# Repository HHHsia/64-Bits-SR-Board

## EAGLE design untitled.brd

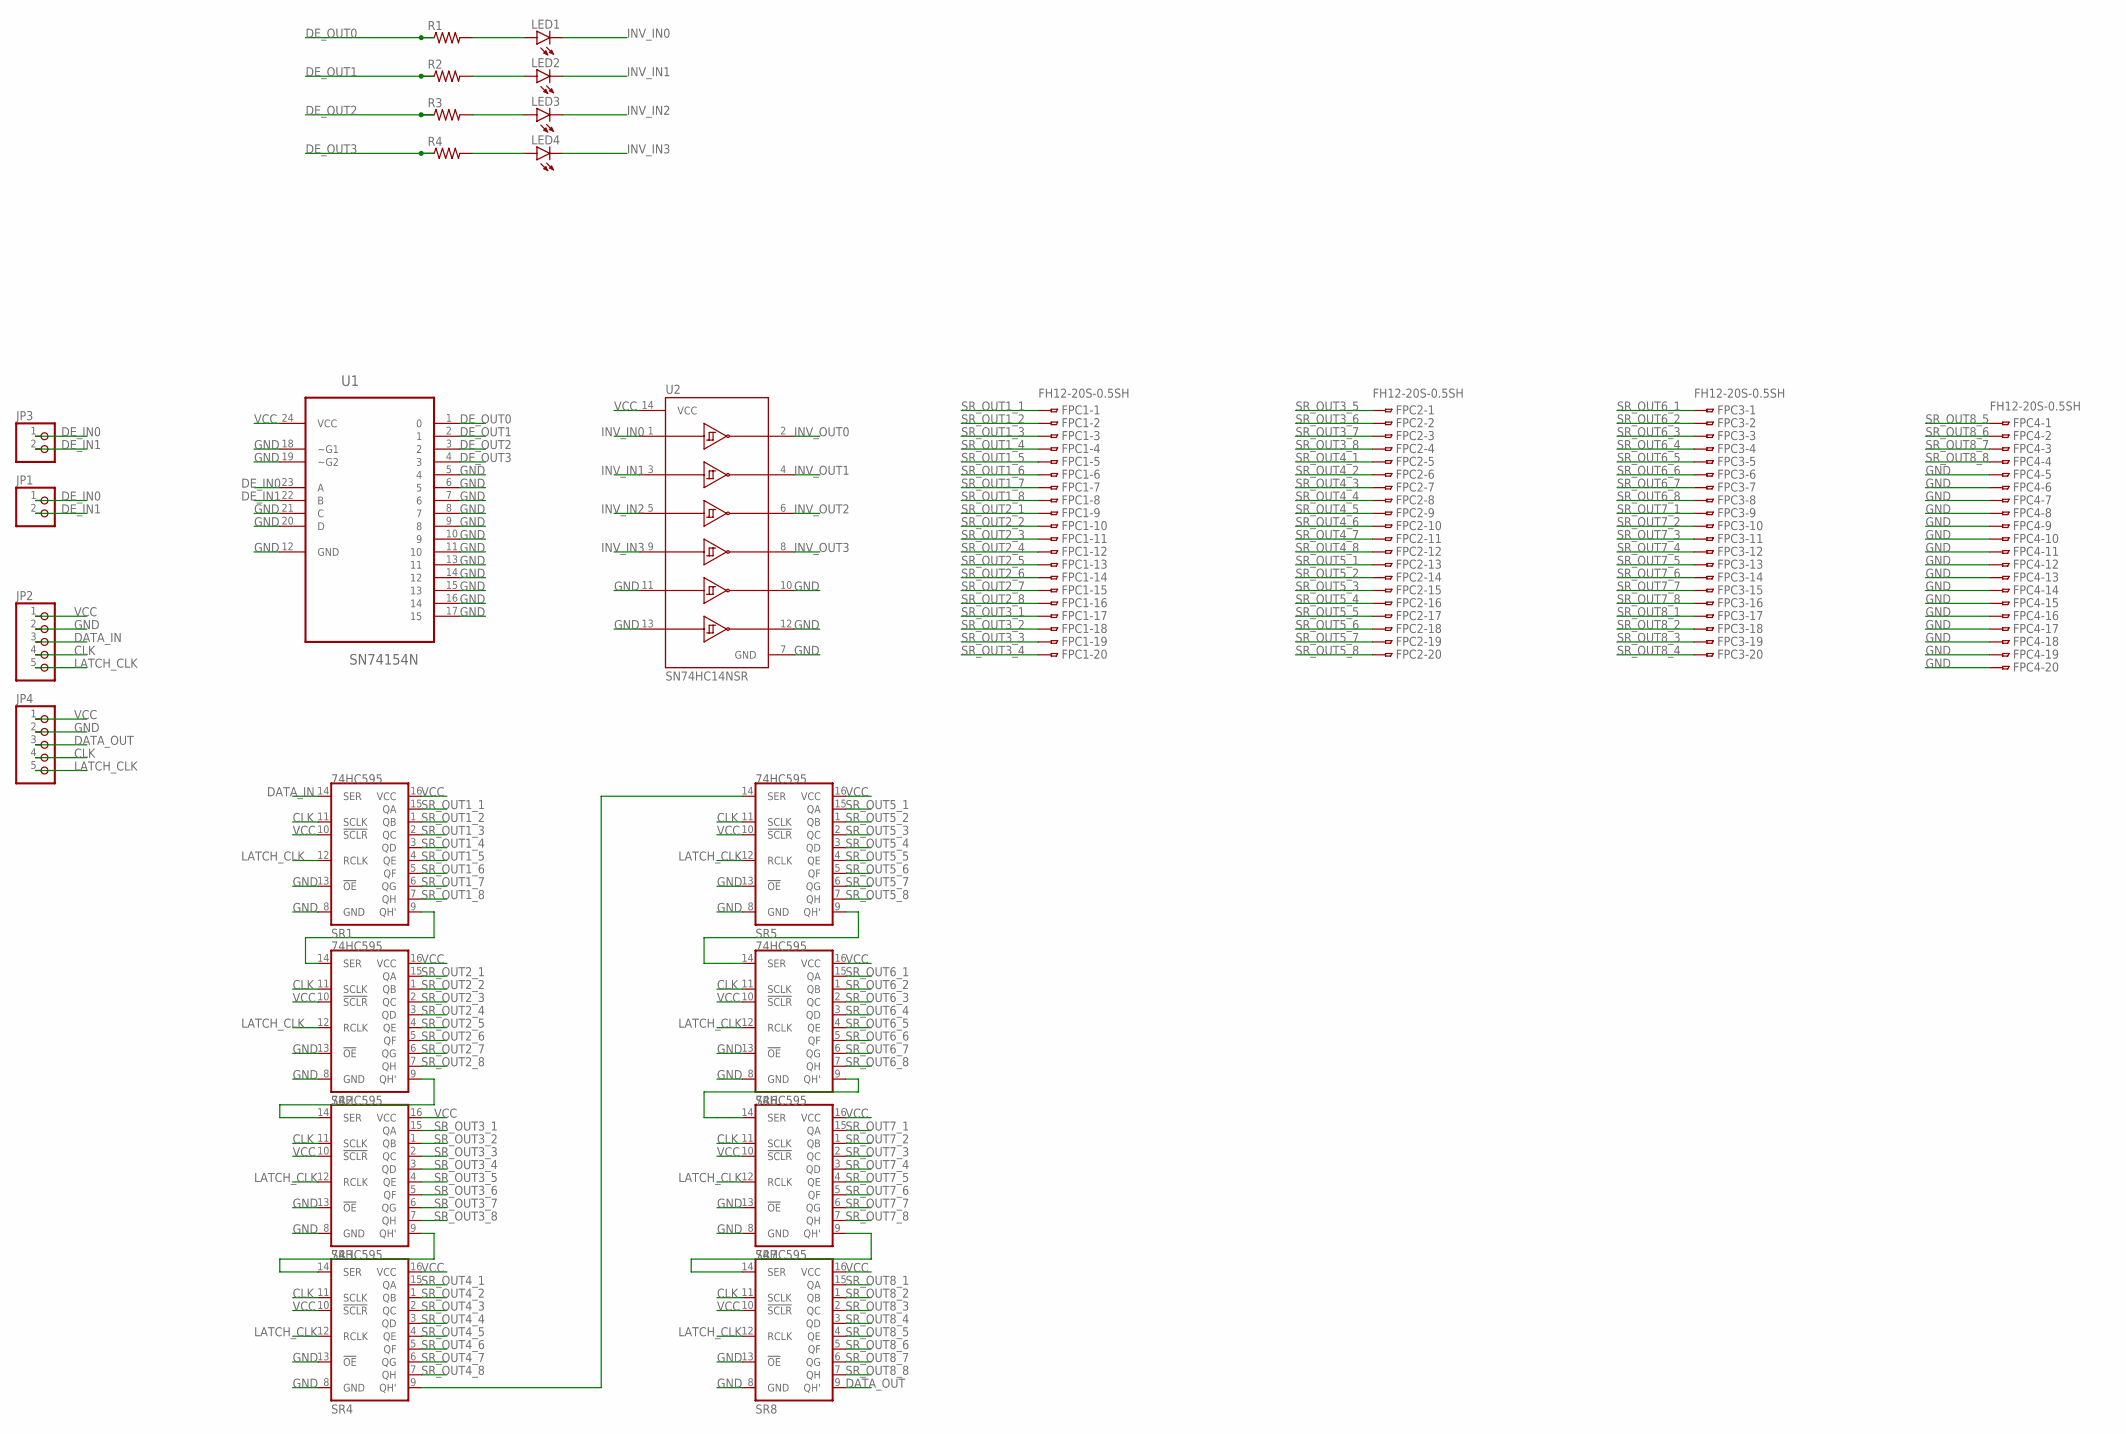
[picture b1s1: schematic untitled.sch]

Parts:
FPC1, FPC2, FPC3, FPC4: FH12-20S-0.5SH
JP1, JP3: PINHD-1X2; 1X02
JP2, JP4: PINHD-1X5; 1X05
LED1, LED2, LED3, LED4: LEDCHIPLED_0805; CHIPLED_0805
R1, R2, R3, R4: R-US_R0805; R0805
SR1, SR2, SR3, SR4, SR5, SR6, SR7, SR8: 74HC595; SO16
U1: SN74154N; DIP254P1080X508-24
U2: SN74HC14NSR; SOP127P780X200-14N

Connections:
CLK: JP2.4, JP4.4, SR1.11 (SCLK), SR2.11 (SCLK), SR3.11 (SCLK), SR4.11 (SCLK), SR5.11 (SCLK), SR6.11 (SCLK), SR7.11 (SCLK), SR8.11 (SCLK)
DATA_IN: JP2.3, SR1.14 (SER)
DATA_OUT: JP4.3, SR8.9 (QH')
DE_IN0: JP1.1, JP3.1, U1.23 (A)
DE_IN1: JP1.2, JP3.2, U1.22 (B)
DE_OUT0: R1.1, U1.1 (0)
DE_OUT1: R2.1, U1.2 (1)
DE_OUT2: R3.1, U1.3 (2)
DE_OUT3: R4.1, U1.4 (3)
GND: FPC4.5, FPC4.6, FPC4.7, FPC4.8, FPC4.9, FPC4.10, FPC4.11, FPC4.12, FPC4.13, FPC4.14, FPC4.15, FPC4.16, FPC4.17, FPC4.18, FPC4.19, FPC4.20, JP2.2, JP4.2, SR1.8 (GND), SR1.13 (!OE), SR2.8 (GND), SR2.13 (!OE), SR3.8 (GND), SR3.13 (!OE), SR4.8 (GND), SR4.13 (!OE), SR5.8 (GND), SR5.13 (!OE), SR6.8 (GND), SR6.13 (!OE), SR7.8 (GND), SR7.13 (!OE), SR8.8 (GND), SR8.13 (!OE), U1.5 (4), U1.6 (5), U1.7 (6), U1.8 (7), U1.9 (8), U1.10 (9), U1.11 (10), U1.12 (GND), U1.13 (11), U1.14 (12), U1.15 (13), U1.16 (14), U1.17 (15), U1.18 (~G1), U1.19 (~G2), U1.20 (D), U1.21 (C), U2.7 (GND), U2.10 (5Y), U2.11 (5A), U2.12 (6Y), U2.13 (6A)
INV_IN0: LED1.C, U2.1 (1A)
INV_IN1: LED2.C, U2.3 (2A)
INV_IN2: LED3.C, U2.5 (3A)
INV_IN3: LED4.C, U2.9 (4A)
INV_OUT0: U2.2 (1Y)
INV_OUT1: U2.4 (2Y)
INV_OUT2: U2.6 (3Y)
INV_OUT3: U2.8 (4Y)
LATCH_CLK: JP2.5, JP4.5, SR1.12 (RCLK), SR2.12 (RCLK), SR3.12 (RCLK), SR4.12 (RCLK), SR5.12 (RCLK), SR6.12 (RCLK), SR7.12 (RCLK), SR8.12 (RCLK)
unnamed: SR1.9 (QH'), SR2.14 (SER)
unnamed: LED1.A, R1.2
unnamed: LED2.A, R2.2
unnamed: LED3.A, R3.2
unnamed: LED4.A, R4.2
unnamed: SR2.9 (QH'), SR3.14 (SER)
unnamed: SR3.9 (QH'), SR4.14 (SER)
unnamed: SR7.9 (QH'), SR8.14 (SER)
unnamed: SR6.9 (QH'), SR7.14 (SER)
unnamed: SR4.9 (QH'), SR5.14 (SER)
unnamed: SR5.9 (QH'), SR6.14 (SER)
SR_OUT1_1: FPC1.1, SR1.15 (QA)
SR_OUT1_2: FPC1.2, SR1.1 (QB)
SR_OUT1_3: FPC1.3, SR1.2 (QC)
SR_OUT1_4: FPC1.4, SR1.3 (QD)
SR_OUT1_5: FPC1.5, SR1.4 (QE)
SR_OUT1_6: FPC1.6, SR1.5 (QF)
SR_OUT1_7: FPC1.7, SR1.6 (QG)
SR_OUT1_8: FPC1.8, SR1.7 (QH)
SR_OUT2_1: FPC1.9, SR2.15 (QA)
SR_OUT2_2: FPC1.10, SR2.1 (QB)
SR_OUT2_3: FPC1.11, SR2.2 (QC)
SR_OUT2_4: FPC1.12, SR2.3 (QD)
SR_OUT2_5: FPC1.13, SR2.4 (QE)
SR_OUT2_6: FPC1.14, SR2.5 (QF)
SR_OUT2_7: FPC1.15, SR2.6 (QG)
SR_OUT2_8: FPC1.16, SR2.7 (QH)
SR_OUT3_1: FPC1.17, SR3.15 (QA)
SR_OUT3_2: FPC1.18, SR3.1 (QB)
SR_OUT3_3: FPC1.19, SR3.2 (QC)
SR_OUT3_4: FPC1.20, SR3.3 (QD)
SR_OUT3_5: FPC2.1, SR3.4 (QE)
SR_OUT3_6: FPC2.2, SR3.5 (QF)
SR_OUT3_7: FPC2.3, SR3.6 (QG)
SR_OUT3_8: FPC2.4, SR3.7 (QH)
SR_OUT4_1: FPC2.5, SR4.15 (QA)
SR_OUT4_2: FPC2.6, SR4.1 (QB)
SR_OUT4_3: FPC2.7, SR4.2 (QC)
SR_OUT4_4: FPC2.8, SR4.3 (QD)
SR_OUT4_5: FPC2.9, SR4.4 (QE)
SR_OUT4_6: FPC2.10, SR4.5 (QF)
SR_OUT4_7: FPC2.11, SR4.6 (QG)
SR_OUT4_8: FPC2.12, SR4.7 (QH)
SR_OUT5_1: FPC2.13, SR5.15 (QA)
SR_OUT5_2: FPC2.14, SR5.1 (QB)
SR_OUT5_3: FPC2.15, SR5.2 (QC)
SR_OUT5_4: FPC2.16, SR5.3 (QD)
SR_OUT5_5: FPC2.17, SR5.4 (QE)
SR_OUT5_6: FPC2.18, SR5.5 (QF)
SR_OUT5_7: FPC2.19, SR5.6 (QG)
SR_OUT5_8: FPC2.20, SR5.7 (QH)
SR_OUT6_1: FPC3.1, SR6.15 (QA)
SR_OUT6_2: FPC3.2, SR6.1 (QB)
SR_OUT6_3: FPC3.3, SR6.2 (QC)
SR_OUT6_4: FPC3.4, SR6.3 (QD)
SR_OUT6_5: FPC3.5, SR6.4 (QE)
SR_OUT6_6: FPC3.6, SR6.5 (QF)
SR_OUT6_7: FPC3.7, SR6.6 (QG)
SR_OUT6_8: FPC3.8, SR6.7 (QH)
SR_OUT7_1: FPC3.9, SR7.15 (QA)
SR_OUT7_2: FPC3.10, SR7.1 (QB)
SR_OUT7_3: FPC3.11, SR7.2 (QC)
SR_OUT7_4: FPC3.12, SR7.3 (QD)
SR_OUT7_5: FPC3.13, SR7.4 (QE)
SR_OUT7_6: FPC3.14, SR7.5 (QF)
SR_OUT7_7: FPC3.15, SR7.6 (QG)
SR_OUT7_8: FPC3.16, SR7.7 (QH)
SR_OUT8_1: FPC3.17, SR8.15 (QA)
SR_OUT8_2: FPC3.18, SR8.1 (QB)
SR_OUT8_3: FPC3.19, SR8.2 (QC)
SR_OUT8_4: FPC3.20, SR8.3 (QD)
SR_OUT8_5: FPC4.1, SR8.4 (QE)
SR_OUT8_6: FPC4.2, SR8.5 (QF)
SR_OUT8_7: FPC4.3, SR8.6 (QG)
SR_OUT8_8: FPC4.4, SR8.7 (QH)
VCC: JP2.1, JP4.1, SR1.10 (!SCLR), SR1.16 (VCC), SR2.10 (!SCLR), SR2.16 (VCC), SR3.10 (!SCLR), SR3.16 (VCC), SR4.10 (!SCLR), SR4.16 (VCC), SR5.10 (!SCLR), SR5.16 (VCC), SR6.10 (!SCLR), SR6.16 (VCC), SR7.10 (!SCLR), SR7.16 (VCC), SR8.10 (!SCLR), SR8.16 (VCC), U1.24 (VCC), U2.14 (VCC)

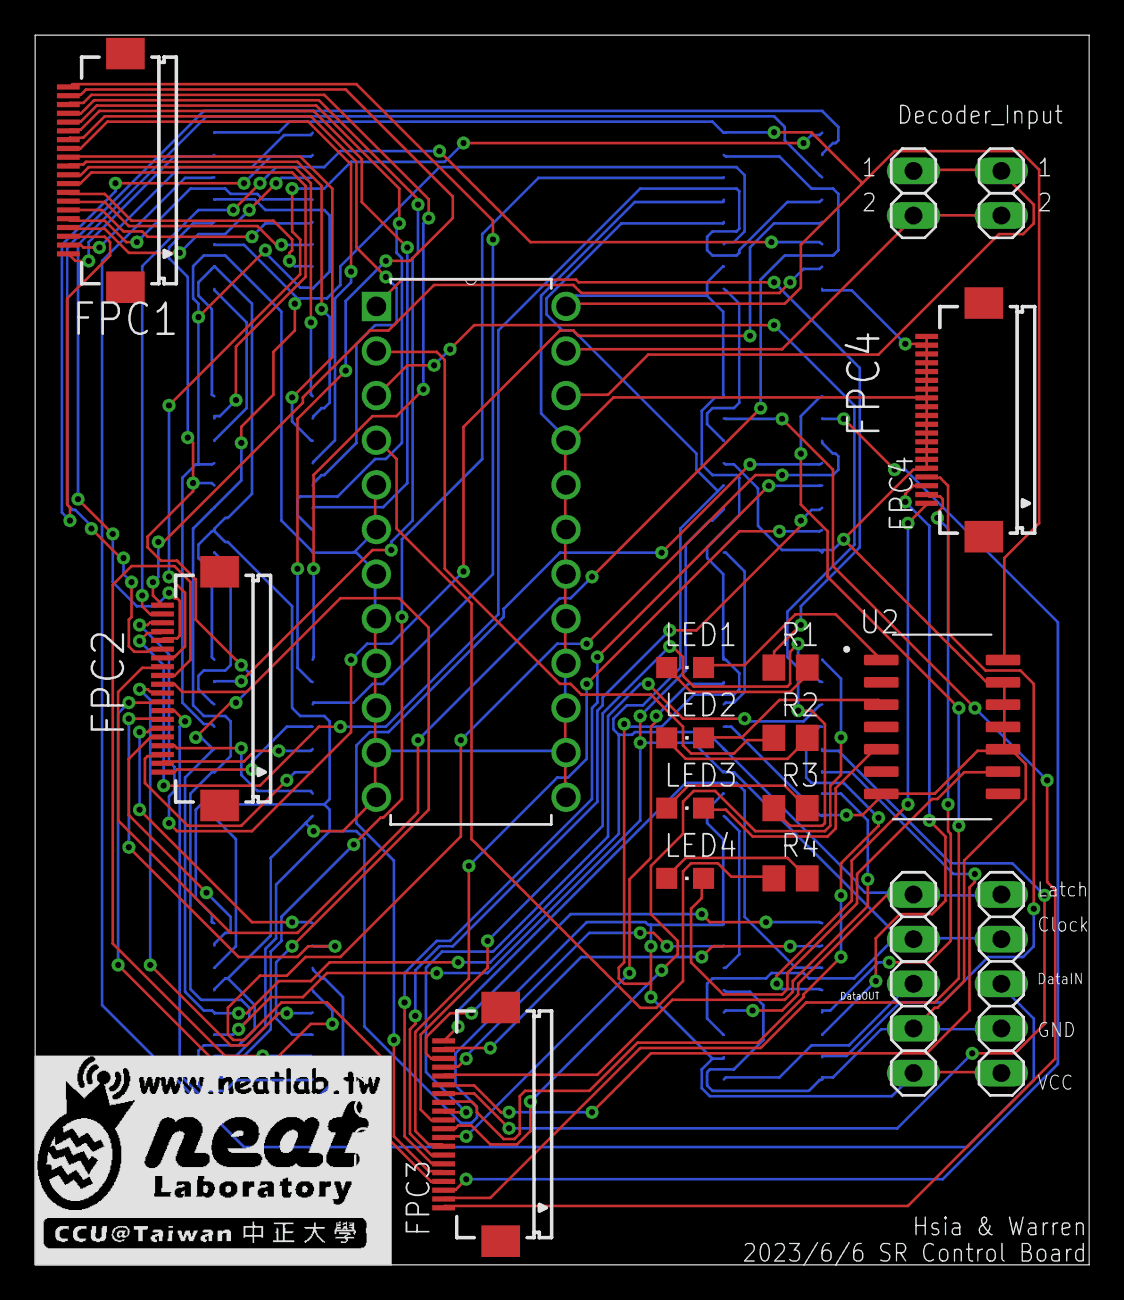
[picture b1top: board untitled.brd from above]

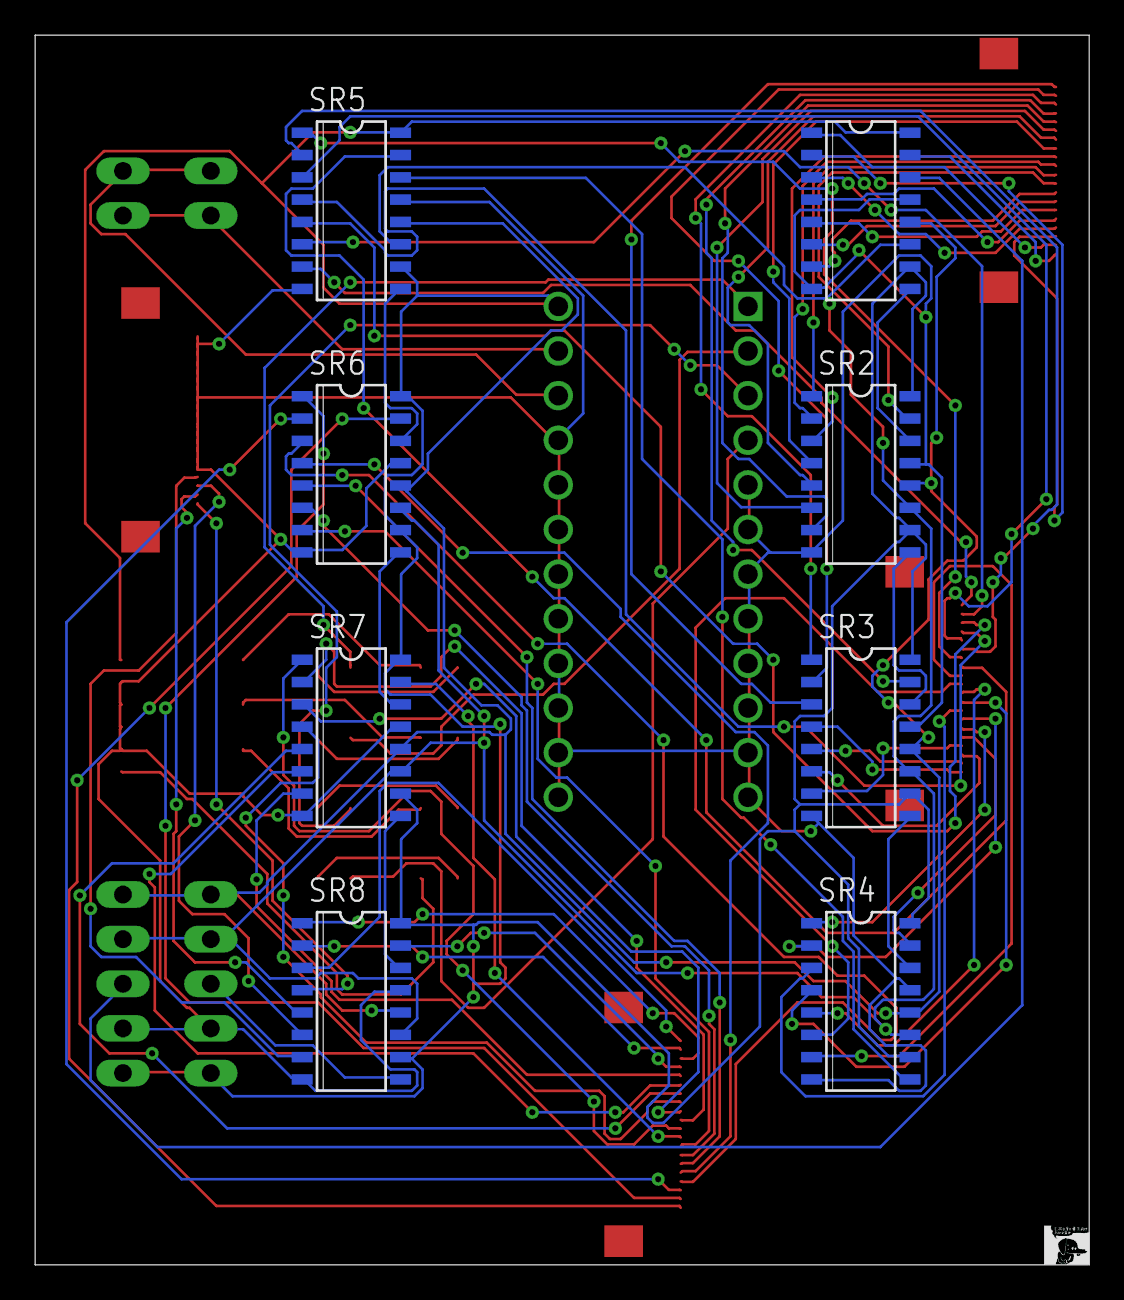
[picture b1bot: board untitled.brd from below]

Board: 2 copper layers, 60.0 x 70.0 mm, 27 parts (8 on the bottom side), 91 nets.

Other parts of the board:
LOGO: LOGO_SCALE_2.0

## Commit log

2024-07-05 0407
2024-07-05 0418
